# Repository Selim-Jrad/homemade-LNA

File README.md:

**Simple LNA for 162-163MHz**
**Schematics**

**PCB Layout**

**3D View**

btw this was a school project
that's why I didn't put much thought into it type shii

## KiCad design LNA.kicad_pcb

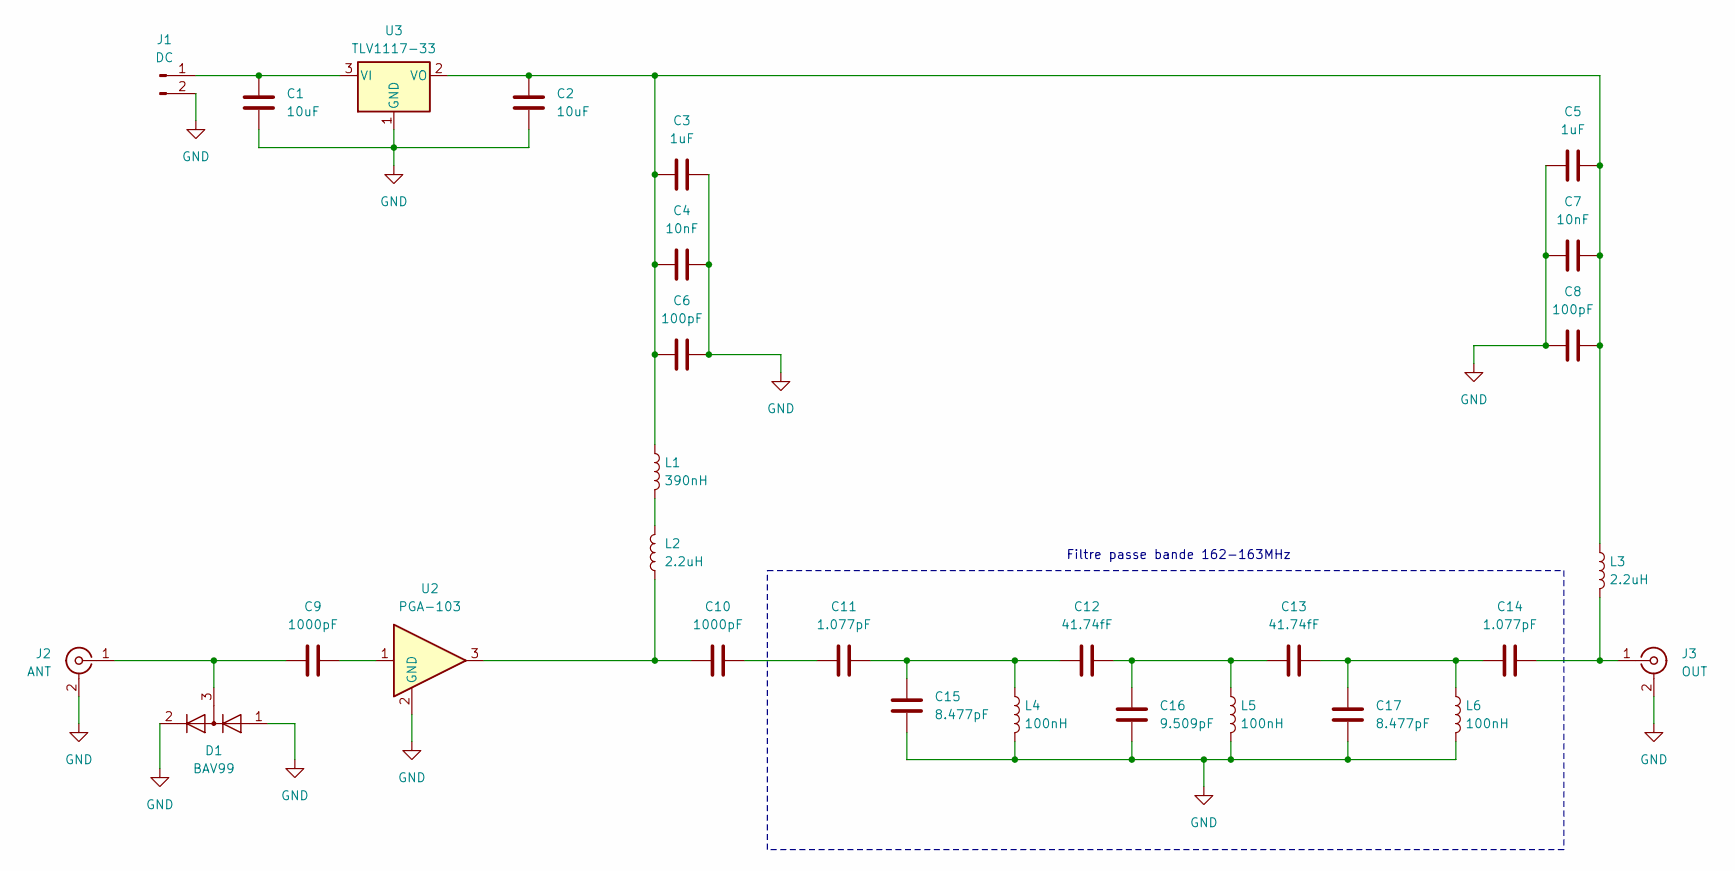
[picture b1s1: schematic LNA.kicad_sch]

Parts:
C1, C2: 10uF; C_0805_2012Metric_Pad1.18x1.45mm_HandSolder
C3, C5: 1uF; C_0805_2012Metric_Pad1.18x1.45mm_HandSolder
C4, C7: 10nF; C_0805_2012Metric_Pad1.18x1.45mm_HandSolder
C6, C8: 100pF; C_0805_2012Metric_Pad1.18x1.45mm_HandSolder
C9, C10: 1000pF; C_0805_2012Metric_Pad1.18x1.45mm_HandSolder
C11, C14: 1.077pF; C_0805_2012Metric_Pad1.18x1.45mm_HandSolder
C12, C13: 41.74fF; C_0805_2012Metric_Pad1.18x1.45mm_HandSolder
C15, C17: 8.477pF; C_0805_2012Metric_Pad1.18x1.45mm_HandSolder
C16: 9.509pF; C_0805_2012Metric_Pad1.18x1.45mm_HandSolder
D1: BAV99; SOT-23
J1: DC; AMASS_XT30UPB-M_1x02_P5.0mm_Vertical
J2: ANT; SMA_Molex_73251-1153_EdgeMount_Horizontal
J3: OUT; SMA_Molex_73251-1153_EdgeMount_Horizontal
L1: 390nH; L_1210_3225Metric_Pad1.42x2.65mm_HandSolder
L2, L3: 2.2uH; L_1210_3225Metric_Pad1.42x2.65mm_HandSolder
L4, L5, L6: 100nH; L_1210_3225Metric_Pad1.42x2.65mm_HandSolder
U2: PGA-103; SOT-89-3
U3: TLV1117-33; SOT-223-3_TabPin2

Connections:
GND: C1.1, C2.1, C3.1, C4.1, C5.1, C6.1, C7.1, C8.1, C15.1, C16.1, C17.1, D1.1 (K), D1.2 (A), J1.2, J2.2 (Ext), J3.2 (Ext), L4.2, L5.2, L6.2, U2.2 (GND), U3.1 (GND)
unnamed: C9.2, U2.1
unnamed: C10.1, L2.1, U2.3
unnamed: C10.2, C11.1
unnamed: C11.2, C12.1, C15.2, L4.1
unnamed: C12.2, C13.1, C16.2, L5.1
unnamed: C13.2, C14.1, C17.2, L6.1
unnamed: C1.2, J1.1, U3.3 (VI)
unnamed: C9.1, D1.3 (K), J2.1 (In)
unnamed: C14.2, J3.1 (In), L3.2
unnamed: L1.2, L2.2
unnamed: C2.2, C3.2, C4.2, C5.2, C6.2, C7.2, C8.2, L1.1, L3.1, U3.2 (VO)

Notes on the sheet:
Filtre passe bande 162-163MHz

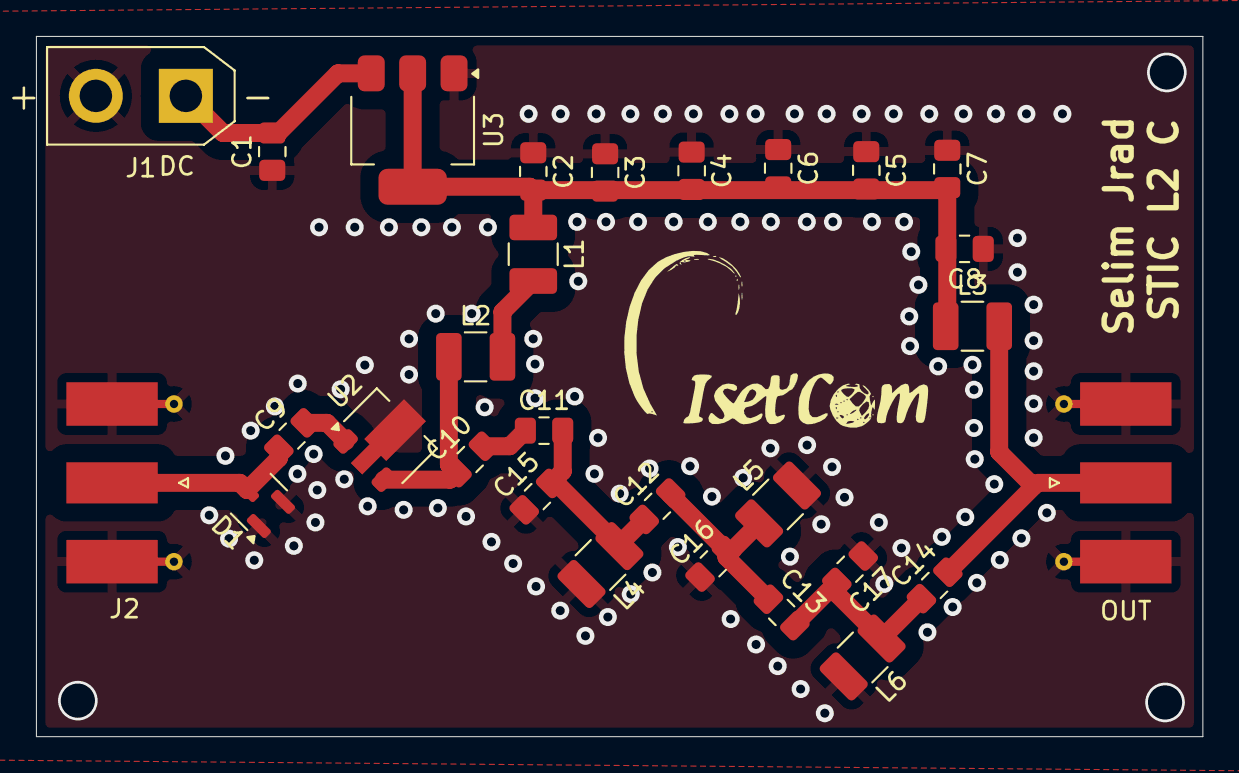
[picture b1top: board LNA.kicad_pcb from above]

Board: 2 copper layers, 64.8 x 38.9 mm, 30 parts (0 on the bottom side), 12 nets.

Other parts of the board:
**: LOGO
